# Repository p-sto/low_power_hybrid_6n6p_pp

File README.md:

Hybrid guitar amp
====

`spice` dir - LTSpice project which allows for circuit simulation.

`models` dir - contains 6N6P model used by LTSpice

`KiCad` dir - contains schematic and pcb for the project - please note that due to my laziness LTSpice schematic does not reflect the same naming convention as KiCad schematic.

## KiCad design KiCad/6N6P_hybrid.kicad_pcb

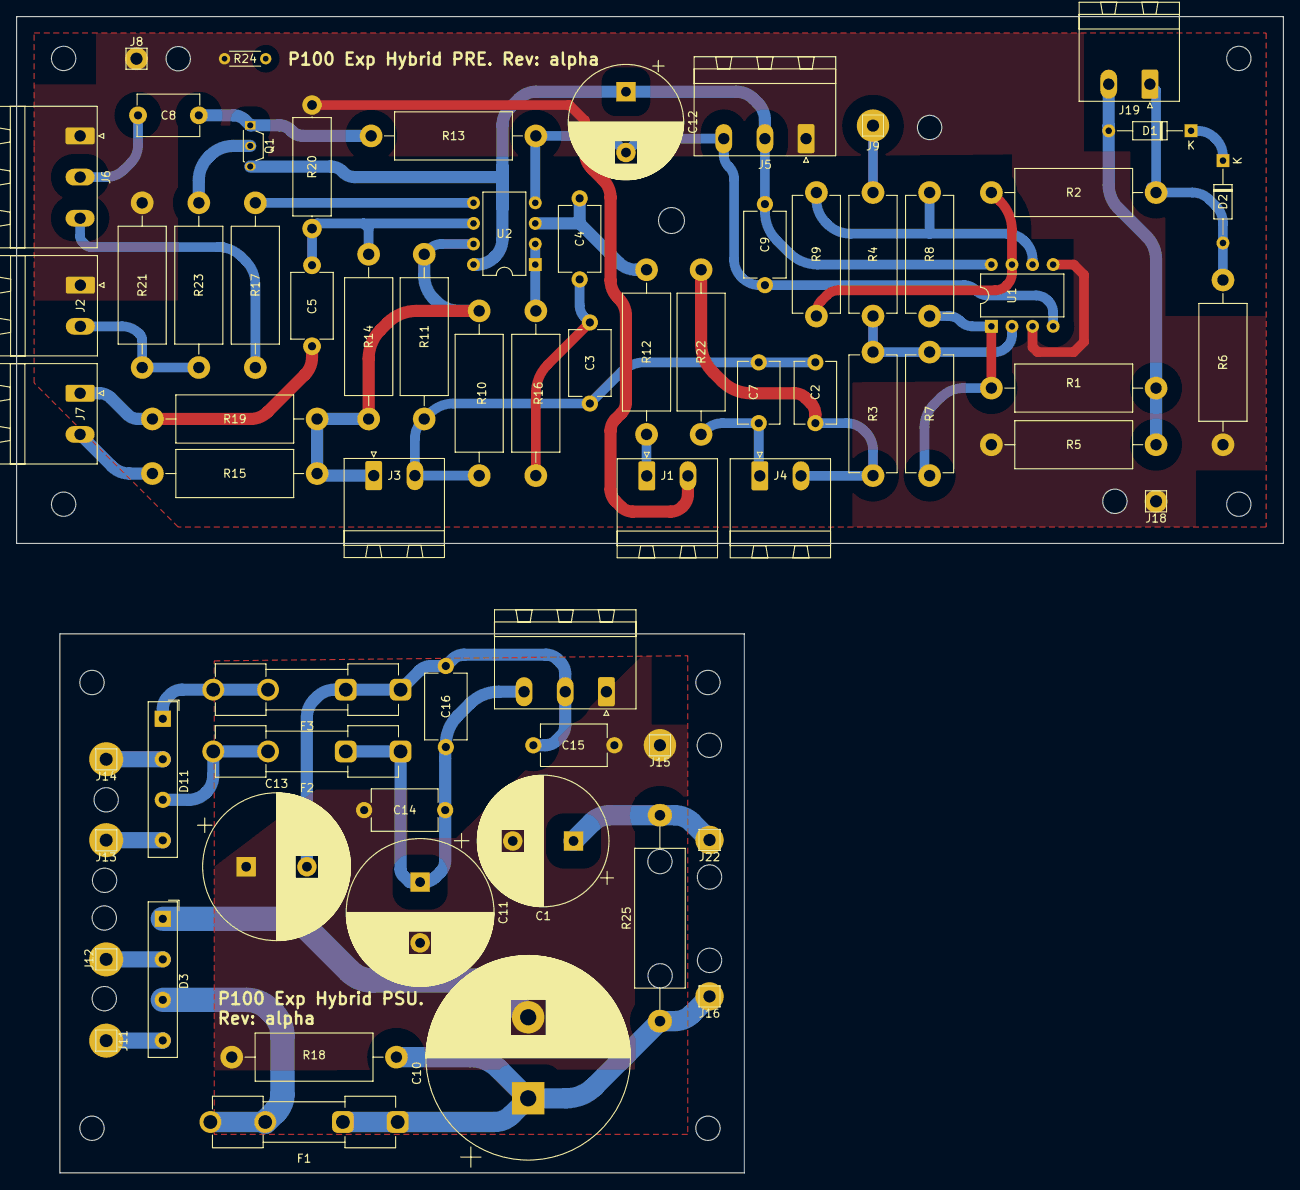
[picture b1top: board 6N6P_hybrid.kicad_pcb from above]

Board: 2 copper layers, 156.3 x 142.7 mm, 69 parts (0 on the bottom side), 40 nets.

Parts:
C1: 68u/350V; CP_Radial_D16.0mm_P7.50mm
C2: 68n; C_Disc_D7.5mm_W5.0mm_P7.50mm
C3, C4: 82n; C_Disc_D8.0mm_W5.0mm_P10.00mm
C5: 220p; C_Disc_D8.0mm_W5.0mm_P10.00mm
C7: 22n; C_Disc_D7.5mm_W5.0mm_P7.50mm
C8: 100n; C_Disc_D7.5mm_W5.0mm_P7.50mm
C9: 10n; C_Disc_D8.0mm_W5.0mm_P10.00mm
C10: 100uF/400V; CP_Radial_D25.0mm_P10.00mm_SnapIn
C11, C13: 4700uF/35V; CP_Radial_D18.0mm_P7.50mm
C12: 10u; CP_Radial_D14.0mm_P7.50mm
C14, C15, C16: C; C_Disc_D8.0mm_W5.0mm_P10.00mm
D1, D2: ZPDxx; D_DO-35_SOD27_P10.16mm_Horizontal
D3, D11: B40C2300-1500B; Diode_Bridge_19.0x3.5x10.0mm_P5.0mm
F1, F2, F3: Fuse; Fuseholder_Clip-5x20mm_Keystone_3517_Inline_P23.11x6.76mm_D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
J1: MID Select; PhoenixContact_MSTBA_2,5_2-G-5,08_1x02_P5.08mm_Horizontal
J2: Input; PhoenixContact_MSTBA_2,5_2-G-5,08_1x02_P5.08mm_Horizontal
J3: MID Bypass; PhoenixContact_MSTBA_2,5_2-G-5,08_1x02_P5.08mm_Horizontal
J4: Low boost; PhoenixContact_MSTBA_2,5_2-G-5,08_1x02_P5.08mm_Horizontal
J5: PrePower; PhoenixContact_MSTBA_2,5_3-G-5,08_1x03_P5.08mm_Horizontal
J6: Volume; PhoenixContact_MSTBA_2,5_3-G-5,08_1x03_P5.08mm_Horizontal
J7: Hi Cut; PhoenixContact_MSTBA_2,5_2-G-5,08_1x02_P5.08mm_Horizontal
J8, J18: chassis; Pin_D1.1mm_L8.5mm_W2.5mm_FlatFork
J9: OT feedback; Pin_D1.1mm_L8.5mm_W2.5mm_FlatFork
J10: Screw_Terminal_01x03; PhoenixContact_MSTBA_2,5_3-G-5,08_1x03_P5.08mm_Horizontal
J11, J12, J13, J14, J16, J22: Screw_Terminal_01x01; Pin_D1.1mm_L8.5mm_W2.5mm_FlatFork
J15: PSU ground; Pin_D1.1mm_L8.5mm_W2.5mm_FlatFork
J19: TUBE; PhoenixContact_MSTBA_2,5_2-G-5,08_1x02_P5.08mm_Horizontal
Q1: BC107; TO-92S_Wide
R1, R2: 330; R_Axial_DIN0614_L14.3mm_D5.7mm_P20.32mm_Horizontal
R3: 1k; R_Axial_DIN0614_L14.3mm_D5.7mm_P15.24mm_Horizontal
R4: 68k; R_Axial_DIN0614_L14.3mm_D5.7mm_P15.24mm_Horizontal
R5, R6, R19, R22: 1Meg; R_Axial_DIN0614_L14.3mm_D5.7mm_P20.32mm_Horizontal
R7: 18k; R_Axial_DIN0614_L14.3mm_D5.7mm_P15.24mm_Horizontal
R8, R9: 10k; R_Axial_DIN0614_L14.3mm_D5.7mm_P15.24mm_Horizontal
R10: 2k; R_Axial_DIN0614_L14.3mm_D5.7mm_P20.32mm_Horizontal
R11, R17: 1k; R_Axial_DIN0614_L14.3mm_D5.7mm_P20.32mm_Horizontal
R12: 27k; R_Axial_DIN0614_L14.3mm_D5.7mm_P20.32mm_Horizontal
R13, R23: 10k; R_Axial_DIN0614_L14.3mm_D5.7mm_P20.32mm_Horizontal
R14: 100k; R_Axial_DIN0614_L14.3mm_D5.7mm_P20.32mm_Horizontal
R15: 15k; R_Axial_DIN0614_L14.3mm_D5.7mm_P20.32mm_Horizontal
R16: 220; R_Axial_DIN0614_L14.3mm_D5.7mm_P20.32mm_Horizontal
R18: R; R_Axial_DIN0614_L14.3mm_D5.7mm_P20.32mm_Horizontal
R20: 12k; R_Axial_DIN0414_L11.9mm_D4.5mm_P15.24mm_Horizontal
R21: 330k; R_Axial_DIN0614_L14.3mm_D5.7mm_P20.32mm_Horizontal
R24: 0; R_Axial_DIN0204_L3.6mm_D1.6mm_P5.08mm_Horizontal
R25: R; R_Axial_DIN0617_L17.0mm_D6.0mm_P25.40mm_Horizontal
U1, U2: LTC1151CN8; DIP-8_W7.62mm

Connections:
GND: J1.2, J2.1, J5.1, J6.1, J8.1, J18.1, R5.2, R6.1, R20.2, R21.1, R24.1, U1.3 (+), U1.5 (+)
GND2: C1.2, C10.2, C11.2, C13.1, C14.1, C15.2, D3.1 (-), J10.1, J15.1, R18.1
unnamed: C3.1, C4.2, R16.2
unnamed: D1.2 (A), J19.2, R1.2, R5.1
unnamed: D1.1 (K), D2.1 (K)
unnamed: D2.2 (A), J19.1, R2.2, R6.2
unnamed: D3.3 (+), F1.2
unnamed: D11.3 (+), F2.2
unnamed: D11.1 (-), F3.2
unnamed: J1.1, R12.2
unnamed: J2.2, R21.2, R23.2
unnamed: J3.1, R10.1, R11.1, R14.2, R15.2, R19.2, U2.7
unnamed: C2.1, C3.2, C7.1, J3.2, R10.2, R11.2
unnamed: C7.2, J4.1, R22.1
unnamed: C2.2, J4.2, R3.2, R22.2
unnamed: C8.2, J6.2
unnamed: J6.3, R17.1
unnamed: C5.2, J7.1, R19.1
unnamed: J7.2, R15.1
unnamed: J9.1, R4.2
unnamed: C13.2, C15.1, C16.1, F3.1, J10.2
unnamed: C11.1, C14.2, C16.2, F2.1, J10.3
unnamed: D3.4, J11.1
unnamed: D3.2, J12.1
unnamed: D11.4, J13.1
unnamed: D11.2, J14.1
unnamed: C10.1, F1.1, J16.1, R18.2, R25.1
unnamed: C1.1, J22.1, R25.2
unnamed: Q1.2 (B), R23.1
unnamed: C8.1, Q1.1 (E), R13.2
unnamed: R1.1, R7.2, R8.2, U1.1
unnamed: R2.1, R9.2, U1.7
unnamed: R3.1, R4.1, R7.1, U1.2 (-)
unnamed: R8.1, R9.1, U1.6 (-)
unnamed: C4.1, R12.1, U2.3 (+)
unnamed: R16.1, U2.1, U2.2 (-)
unnamed: R17.2, U2.5 (+)
unnamed: C5.1, R14.1, R20.1, U2.6 (-)
V++: C9.2, C12.1, J5.2, Q1.3 (C), U1.8 (V+), U2.8 (V+)
V--: C9.1, C12.2, J5.3, R13.1, U1.4 (V-), U2.4 (V-)
